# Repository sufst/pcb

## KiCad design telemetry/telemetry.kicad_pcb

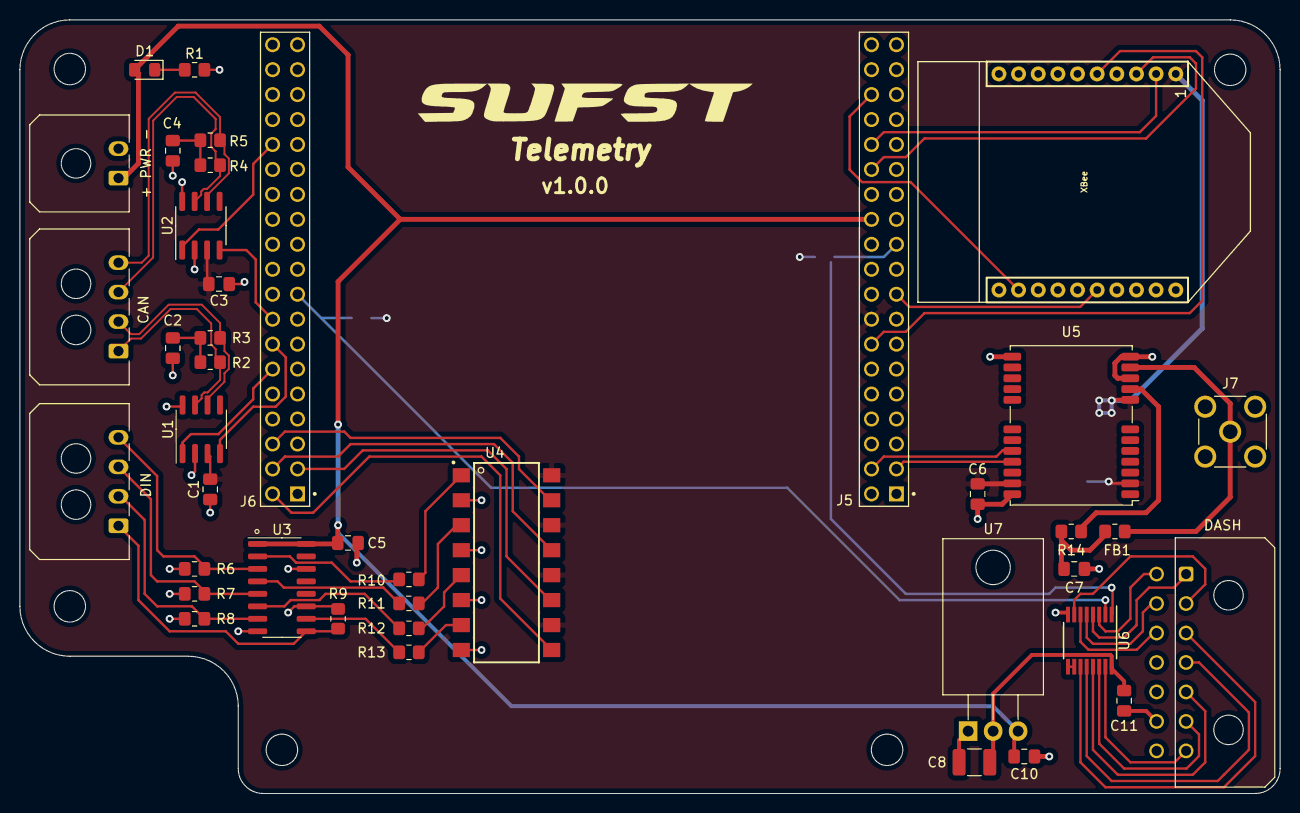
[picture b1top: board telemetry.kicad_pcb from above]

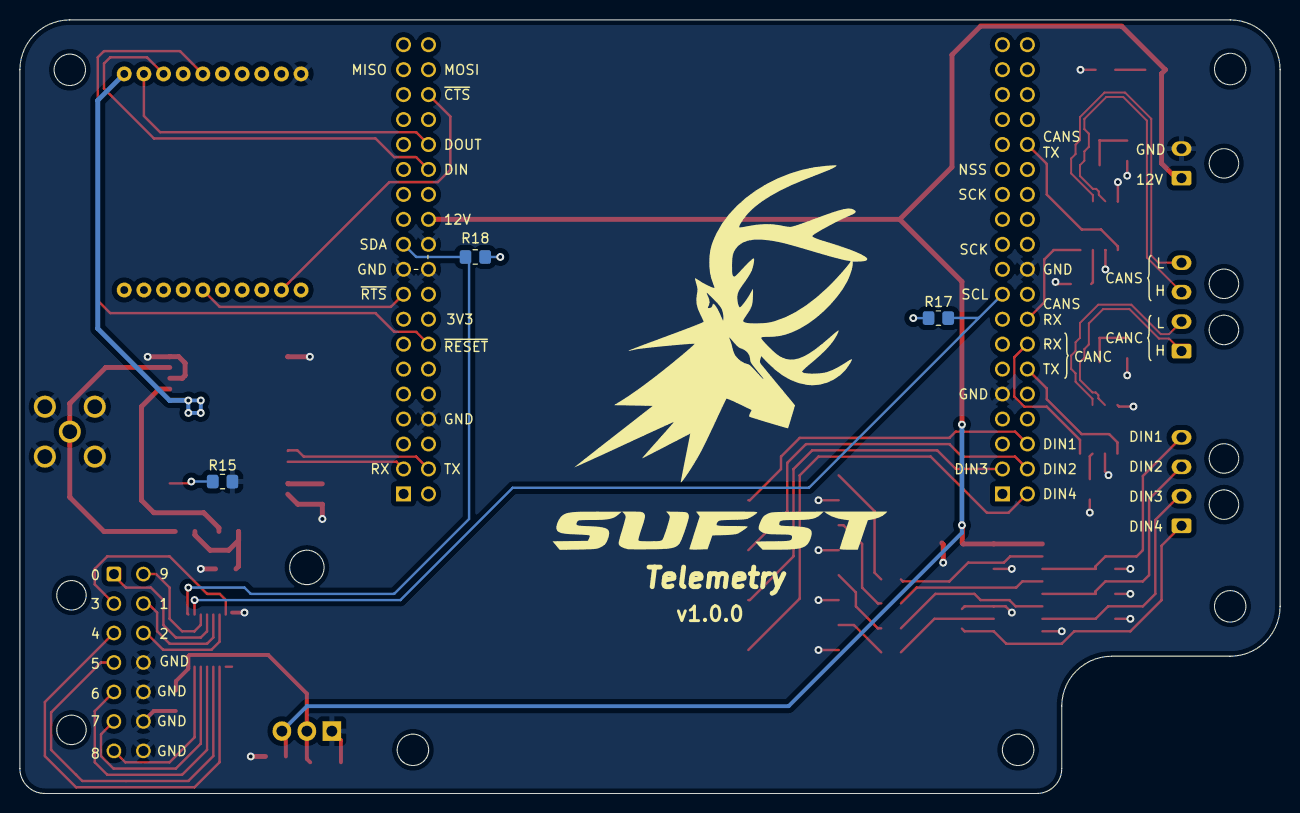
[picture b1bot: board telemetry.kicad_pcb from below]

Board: 2 copper layers, 128.3 x 78.7 mm, 49 parts (3 on the bottom side), 53 nets.

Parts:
C1, C3, C5, C10, C11: 100n; C_0805_2012Metric_Pad1.18x1.45mm_HandSolder
C2, C4: 4.7n; C_0805_2012Metric_Pad1.18x1.45mm_HandSolder
C6: 100nF; C_0805_2012Metric_Pad1.18x1.45mm_HandSolder
C7: 47pF; C_0805_2012Metric_Pad1.18x1.45mm_HandSolder
C8: 10u; C_1210_3225Metric_Pad1.33x2.70mm_HandSolder
D1: LED; LED_0805_2012Metric_Pad1.15x1.40mm_HandSolder
FB1: 120; R_0805_2012Metric_Pad1.20x1.40mm_HandSolder
H1, H2, H3, H4, H5: M3; MountingHole_3.2mm_M3
J1: PWR; Molex_Micro-Fit_3.0_43650-0200_1x02_P3.00mm_Horizontal
J2: MCU_DIN; Molex_Micro-Fit_3.0_43650-0400_1x04_P3.00mm_Horizontal
J3: CAN; Molex_Micro-Fit_3.0_43650-0400_1x04_P3.00mm_Horizontal
J4: XBee; XBEE
J5: CN7; NUCLEO-F446RE-2x19-CON
J6: CN10; NUCLEO-F446RE-2x19-CON
J7: Conn_Coaxial; SMA_Molex_73251-2200_Horizontal
J8: Dash 7 Segment; Molex_Micro-Fit_3.0_43045-1400_2x07_P3.00mm_Horizontal
R1: 3.3k; R_0805_2012Metric_Pad1.20x1.40mm_HandSolder
R2, R3, R4, R5: 60R; R_0805_2012Metric_Pad1.20x1.40mm_HandSolder
R6, R7, R8, R9: 10k; R_0805_2012Metric_Pad1.20x1.40mm_HandSolder
R10, R11, R12, R13: 1k; R_0805_2012Metric_Pad1.20x1.40mm_HandSolder
R14: 33; R_0805_2012Metric_Pad1.20x1.40mm_HandSolder
R15: DNP; R_0805_2012Metric_Pad1.20x1.40mm_HandSolder
R17, R18: 4k7; R_0805_2012Metric_Pad1.20x1.40mm_HandSolder
U1, U2: MAX3051ESA+; SOIC-8_3.9x4.9mm_P1.27mm
U3: HCF4010; SOIC-16_3.9x9.9mm_P1.27mm
U4: ILQ615-4X009T; SOIC254P1005X380-16N
U5: NEO-M9N; ublox_NEO
U6: MAX6958BAEE+T; QSOP-16_3.9x4.9mm_P0.635mm
U7: LD33CV; TO-220-3_Horizontal_TabDown

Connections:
+3V3: C1.2, C3.2, C6.2, J4.1, J5.16, R15.1, R17.1, R18.1, U1.3 (VDD), U2.3 (VDD), U4.10, U4.12, U4.14, U4.16, U5.2 (D_SEL), U5.8 (~RESET), U5.23 (VCC)
+12V: C5.2, C10.2, D1.2 (A), J1.1, J5.24, U3.1 (VCC), U3.16 (VDD), U7.3 (VI)
/3V3_LED: C8.1, C11.2, U6.16 (V+), U7.2 (VO)
/CAN-C Bus Transceiver/CAN_RX: J6.14, U1.4 (RXD)
/CAN-C Bus Transceiver/CAN_TX: J6.12, U1.1 (TXD)
/CAN-S Bus Transceiver/CAN_RX: J6.16, U2.4 (RXD)
/CAN-S Bus Transceiver/CAN_TX: J6.30, U2.1 (TXD)
/CAN_C+: J3.1, R2.2, U1.7 (CANH)
/CAN_C-: J3.2, R3.1, U1.6 (CANL)
/CAN_S+: J3.3, R4.2, U2.7 (CANH)
/CAN_S-: J3.4, R5.1, U2.6 (CANL)
/GPS/GPS_RX: J5.3, U5.21 (RXD/SPI_MOSI)
/GPS/GPS_TX: J5.4, U5.20 (TXD/SPI_MISO)
/SEG0: J8.1, U6.4 (DIG0/SEG0)
/SEG1: J8.9, U6.5 (DIG1/SEG1)
/SEG2: J8.10, U6.6 (DIG2/SEG2)
/SEG3: J8.2, U6.7 (DIG3/SEG3)
/SEG4: J8.3, U6.11 (SEG4)
/SEG5: J8.4, U6.12 (SEG5)
/SEG6: J8.5, U6.13 (SEG6)
/SEG7: J8.6, U6.14 (SEG7)
/SEG8: J8.7, U6.15 (SEG8)
/SEG9: J8.8, U6.3 (SEG9)
/XBee Module/DIN/`CONFIG/DIO14: J4.3, J5.28
/XBee Module/DOUT/DIO13: J4.2, J5.30
/XBee Module/~CTS: J4.12, J5.34
/XBee Module/~RESET: J4.5, J5.14
/XBee Module/~RTS: J4.16, J5.17
/input shift/DIN_1: J2.4, R6.2, U3.3 (Ain)
/input shift/DIN_2: J2.3, R7.2, U3.5 (Bin)
/input shift/DIN_3: J2.2, R8.2, U3.7 (Cin)
/input shift/DIN_4: J2.1, R9.2, U3.9 (Din)
/input shift/DOUT_1: J6.6, U4.15
/input shift/DOUT_2: J6.4, U4.13
/input shift/DOUT_3: J6.3, U4.11
/input shift/DOUT_4: J6.2, U4.9
/mcu/I2C1_SCL: J6.17, R17.2, U6.2 (SCL)
/mcu/I2C1_SDA: J5.21, R18.2, U6.1 (SDA)
GND: C1.1, C2.2, C3.1, C4.2, C5.1, C6.1, C7.1, C8.2, C10.1, C11.1, J1.2, J4.10, J5.8, J5.19, J5.20, J5.22, J6.9, J6.20, J7.2 (Ext), J8.11, J8.12, J8.13, J8.14, R1.2, R6.1, R7.1, R8.1, R9.1, R15.2, U1.2 (GND), U1.8 (RS), U2.2 (GND), U2.8 (RS), U3.8 (VSS), U3.11 (Ein), U3.14 (Fin), U4.2, U4.4, U4.6, U4.8, U5.10 (GND), U5.12 (GND), U5.13 (GND), U5.24 (GND), U6.8 (GND), U7.1 (GND)
unnamed: C2.1, R2.1, R3.2
unnamed: C4.1, R4.1, R5.2
unnamed: C7.2, FB1.1, R14.2
unnamed: D1.1 (K), R1.1
unnamed: FB1.2, J7.1 (In), U5.11 (RF_IN)
unnamed: R10.1, U3.2 (Aout)
unnamed: R10.2, U4.1
unnamed: R11.1, U3.4 (Bout)
unnamed: R11.2, U4.3
unnamed: R12.1, U3.6 (Cout)
unnamed: R12.2, U4.5
unnamed: R13.1, U3.10 (Dout)
unnamed: R13.2, U4.7
unnamed: R14.1, U5.9 (VCC_RF)

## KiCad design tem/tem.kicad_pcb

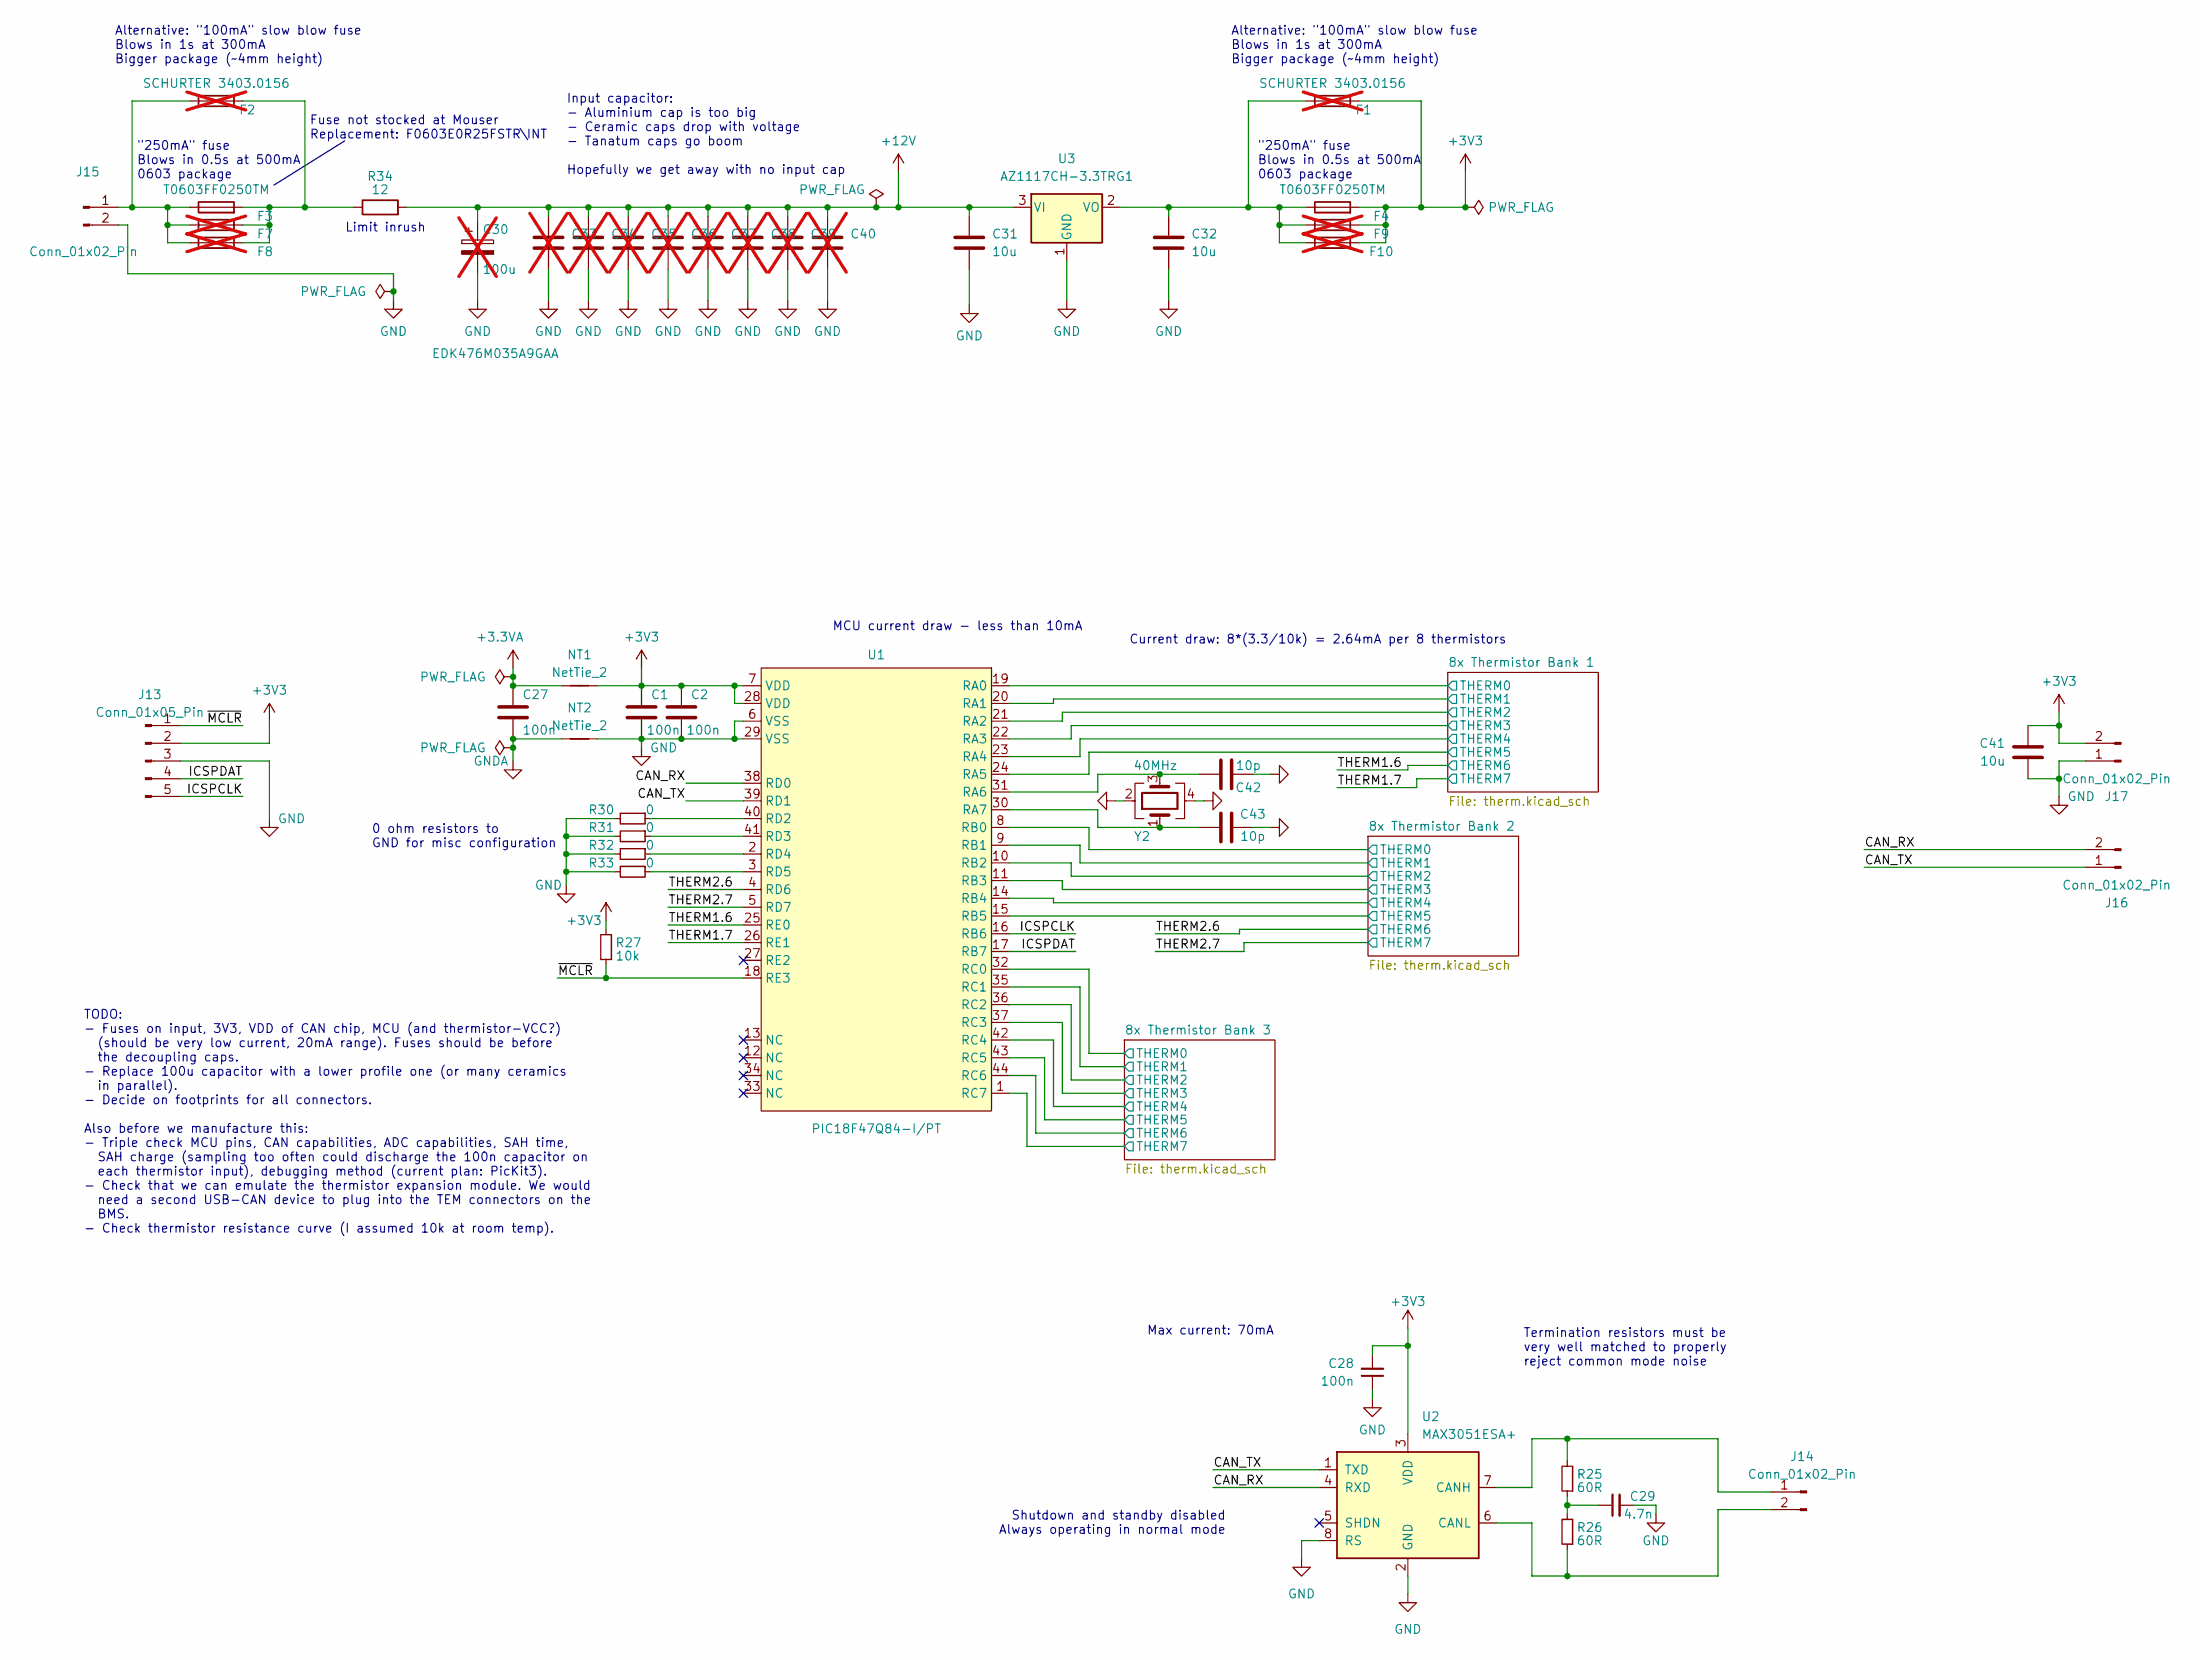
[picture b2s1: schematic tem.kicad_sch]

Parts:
C1, C2, C27, C28: 100n; C_0805_2012Metric_Pad1.18x1.45mm_HandSolder
C29: 4.7n; C_0805_2012Metric_Pad1.18x1.45mm_HandSolder
C30: 100u; CP_Elec_6.3x5.4; Part EDK476M035A9GAA; not fitted
C31, C32, C41: 10u; C_0805_2012Metric_Pad1.18x1.45mm_HandSolder
C33, C34, C35, C36, C37, C38, C39, C40: C_1206_3216Metric_Pad1.33x1.80mm_HandSolder; not fitted
C42, C43: 10p; C_0603_1608Metric_Pad1.08x0.95mm_HandSolder
F1, F2: SCHURTER 3403.0156; Fuse_Schurter_UMT250; not fitted
F3, F4: T0603FF0250TM; Fuse_0603_1608Metric_Pad1.05x0.95mm_HandSolder
F7, F8, F9, F10: T0603FF0250TM; Fuse_0603_1608Metric_Pad1.05x0.95mm_HandSolder; not fitted
J13: Conn_01x05_Pin; Conn5_SMD
J14, J15, J16, J17: Conn_01x02_Pin; Conn2_SMD
NT1, NT2: NetTie_2; R_0805_2012Metric_Pad1.20x1.40mm_HandSolder
R25, R26: 60R; R_0805_2012Metric_Pad1.20x1.40mm_HandSolder
R27: 10k; R_0805_2012Metric_Pad1.20x1.40mm_HandSolder
R30, R31, R32, R33: 0; R_0805_2012Metric_Pad1.20x1.40mm_HandSolder
R34: 12; R_0805_2012Metric_Pad1.20x1.40mm_HandSolder
U1: PIC18F47Q84-I/PT; TQFP-44_10x10mm_P0.8mm
U2: MAX3051ESA+; SOIC-8_3.9x4.9mm_P1.27mm
U3: AZ1117CH-3.3TRG1; SOT-223-3_TabPin2
Y2: 40MHz; Crystal_SMD_SeikoEpson_FA128-4Pin_2.0x1.6mm

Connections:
+3.3VA: C27.1, NT1.1; also elsewhere on the board
+3V3: C1.1, C2.1, C28.2, C41.1, F1.2, F4.2, F9.2, F10.2, J13.2, J17.2, NT1.2, R27.2, U1.7 (VDD), U1.28 (VDD), U2.3 (VDD)
+12V: C30.1, C31.1, C33.1, C34.1, C35.1, C36.1, C37.1, C38.1, C39.1, C40.1, R34.2, U3.3 (VI)
/8x Thermistor Bank 1/THERM0: U1.19 (RA0); also elsewhere on the board
/8x Thermistor Bank 1/THERM1: U1.20 (RA1); also elsewhere on the board
/8x Thermistor Bank 1/THERM2: U1.21 (RA2); also elsewhere on the board
/8x Thermistor Bank 1/THERM3: U1.22 (RA3); also elsewhere on the board
/8x Thermistor Bank 1/THERM4: U1.23 (RA4); also elsewhere on the board
/8x Thermistor Bank 1/THERM5: U1.24 (RA5); also elsewhere on the board
/8x Thermistor Bank 1/THERM6: C42.1, U1.31 (RA6), Y2.3; also elsewhere on the board
/8x Thermistor Bank 1/THERM7: C43.1, U1.30 (RA7), Y2.1; also elsewhere on the board
/8x Thermistor Bank 2/THERM0: U1.8 (RB0); also elsewhere on the board
/8x Thermistor Bank 2/THERM1: U1.9 (RB1); also elsewhere on the board
/8x Thermistor Bank 2/THERM2: U1.10 (RB2); also elsewhere on the board
/8x Thermistor Bank 2/THERM3: U1.11 (RB3); also elsewhere on the board
/8x Thermistor Bank 2/THERM4: U1.14 (RB4); also elsewhere on the board
/8x Thermistor Bank 2/THERM5: U1.15 (RB5); also elsewhere on the board
/8x Thermistor Bank 3/THERM0: U1.32 (RC0); also elsewhere on the board
/8x Thermistor Bank 3/THERM1: U1.35 (RC1); also elsewhere on the board
/8x Thermistor Bank 3/THERM2: U1.36 (RC2); also elsewhere on the board
/8x Thermistor Bank 3/THERM3: U1.37 (RC3); also elsewhere on the board
/8x Thermistor Bank 3/THERM4: U1.42 (RC4); also elsewhere on the board
/8x Thermistor Bank 3/THERM5: U1.43 (RC5); also elsewhere on the board
/8x Thermistor Bank 3/THERM6: U1.44 (RC6); also elsewhere on the board
/8x Thermistor Bank 3/THERM7: U1.1 (RC7); also elsewhere on the board
/CAN_RX: J16.2, U1.38 (RD0), U2.4 (RXD)
/CAN_TX: J16.1, U1.39 (RD1), U2.1 (TXD)
/ICSPCLK: J13.5, U1.16 (RB6)
/ICSPDAT: J13.4, U1.17 (RB7)
/THERM2.6: U1.4 (RD6); also elsewhere on the board
/THERM2.7: U1.5 (RD7); also elsewhere on the board
/~MCLR: J13.1, R27.1, U1.18 (RE3)
GND: C1.2, C2.2, C28.1, C29.2, C30.2, C31.2, C32.2, C33.2, C34.2, C35.2, C36.2, C37.2, C38.2, C39.2, C40.2, C41.2, J13.3, J15.2, J17.1, NT2.2, R30.2, R31.2, R32.2, R33.2, U1.6 (VSS), U1.29 (VSS), U2.2 (GND), U2.8 (RS), U3.1 (GND)
GNDA: C27.2, NT2.1; also elsewhere on the board
unnamed: C29.1, R25.1, R26.2
unnamed: F2.2, F3.2, F7.2, F8.2, R34.1
unnamed: J14.1, R25.2, U2.7 (CANH)
unnamed: J14.2, R26.1, U2.6 (CANL)
unnamed: F2.1, F3.1, F7.1, F8.1, J15.1
unnamed: R30.1, U1.40 (RD2)
unnamed: R31.1, U1.41 (RD3)
unnamed: R32.1, U1.2 (RD4)
unnamed: R33.1, U1.3 (RD5)
unnamed: C32.1, F1.1, F4.1, F9.1, F10.1, U3.2 (VO)

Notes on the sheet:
Alternative: "100mA" slow blow fuse Blows in 1s at 300mA Bigger package (~4mm height)
MCU current draw - less than 10mA
Max current: 70mA
Shutdown and standby disabled Always operating in normal mode
"250mA" fuse Blows in 0.5s at 500mA 0603 package
Input capacitor: - Aluminium cap is too big - Ceramic caps drop with voltage - Tanatum caps go boom Hopefully we get away with no input cap
Current draw: 8*(3.3/10k) = 2.64mA per 8 thermistors
0 ohm resistors to GND for misc configuration
TODO: - Fuses on input, 3V3, VDD of CAN chip, MCU (and thermistor-VCC?) (should be very low current, 20mA range). Fuses should be before the decoupling caps. - Replace 100u capacitor with a lower profile one (or many ceramics in parallel). - Decide on footprints for all connectors. Also before we m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
Fuse not stocked at Mouser Replacement: F0603E0R25FSTR\INT
Limit inrush
Termination resistors must be very well matched to properly reject common mode noise

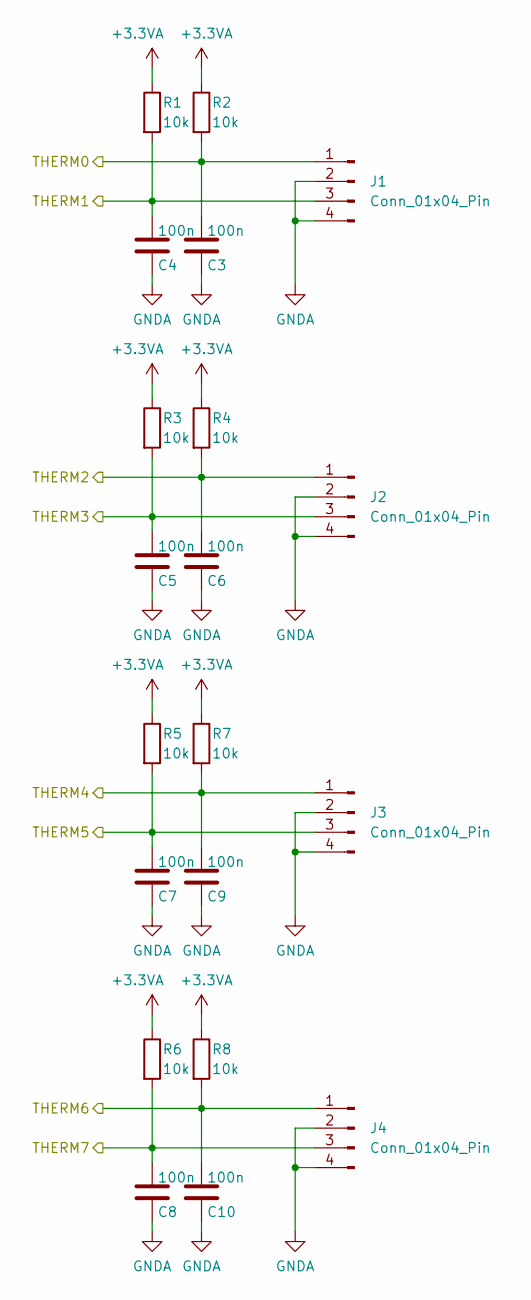
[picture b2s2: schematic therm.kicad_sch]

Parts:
C3, C4, C5, C6, C7, C8, C9, C10: 100n; C_0805_2012Metric_Pad1.18x1.45mm_HandSolder
J1, J2, J3, J4: Conn_01x04_Pin; Thermistor_x2
R1, R2, R3, R4, R5, R6, R7, R8: 10k; R_0805_2012Metric_Pad1.20x1.40mm_HandSolder

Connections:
+3.3VA: R1.1, R2.1, R3.1, R4.1, R5.1, R6.1, R7.1, R8.1; also elsewhere on the board
/8x Thermistor Bank 1/THERM0: C3.1, J1.1, R2.2; also elsewhere on the board
/8x Thermistor Bank 1/THERM1: C4.1, J1.3, R1.2; also elsewhere on the board
/8x Thermistor Bank 1/THERM2: C6.1, J2.1, R4.2; also elsewhere on the board
/8x Thermistor Bank 1/THERM3: C5.1, J2.3, R3.2; also elsewhere on the board
/8x Thermistor Bank 1/THERM4: C9.1, J3.1, R7.2; also elsewhere on the board
/8x Thermistor Bank 1/THERM5: C7.1, J3.3, R5.2; also elsewhere on the board
/8x Thermistor Bank 1/THERM6: C10.1, J4.1, R8.2; also elsewhere on the board
/8x Thermistor Bank 1/THERM7: C8.1, J4.3, R6.2; also elsewhere on the board
GNDA: C3.2, C4.2, C5.2, C6.2, C7.2, C8.2, C9.2, C10.2, J1.2, J1.4, J2.2, J2.4, J3.2, J3.4, J4.2, J4.4; also elsewhere on the board

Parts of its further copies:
C11, C12, C13, C14, C15, C16, C17, C18, C19, C20, C21, C22, C23, C24, C25, C26: 100n; C_0805_2012Metric_Pad1.18x1.45mm_HandSolder
J5, J6, J7, J8, J9, J10, J11, J12: Conn_01x04_Pin; Thermistor_x2
R9, R10, R11, R12, R13, R14, R15, R16, R17, R18, R19, R20, R21, R22, R23, R24: 10k; R_0805_2012Metric_Pad1.20x1.40mm_HandSolder

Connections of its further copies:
+3.3VA: R9.1, R10.1, R11.1, R12.1, R13.1, R14.1, R15.1, R16.1, R17.1, R18.1, R19.1, R20.1, R21.1, R22.1, R23.1, R24.1; also elsewhere on the board
/8x Thermistor Bank 2/THERM0: C15.1, J5.1, R13.2; also elsewhere on the board
/8x Thermistor Bank 2/THERM1: C11.1, J5.3, R9.2; also elsewhere on the board
/8x Thermistor Bank 2/THERM2: C16.1, J6.1, R14.2; also elsewhere on the board
/8x Thermistor Bank 2/THERM3: C12.1, J6.3, R10.2; also elsewhere on the board
/8x Thermistor Bank 2/THERM4: C17.1, J7.1, R15.2; also elsewhere on the board
/8x Thermistor Bank 2/THERM5: C13.1, J7.3, R11.2; also elsewhere on the board
/8x Thermistor Bank 3/THERM0: C23.1, J9.1, R21.2; also elsewhere on the board
/8x Thermistor Bank 3/THERM1: C19.1, J9.3, R17.2; also elsewhere on the board
/8x Thermistor Bank 3/THERM2: C24.1, J10.1, R22.2; also elsewhere on the board
/8x Thermistor Bank 3/THERM3: C20.1, J10.3, R18.2; also elsewhere on the board
/8x Thermistor Bank 3/THERM4: C25.1, J11.1, R23.2; also elsewhere on the board
/8x Thermistor Bank 3/THERM5: C21.1, J11.3, R19.2; also elsewhere on the board
/8x Thermistor Bank 3/THERM6: C26.1, J12.1, R24.2; also elsewhere on the board
/8x Thermistor Bank 3/THERM7: C22.1, J12.3, R20.2; also elsewhere on the board
/THERM2.6: C18.1, J8.1, R16.2; also elsewhere on the board
/THERM2.7: C14.1, J8.3, R12.2; also elsewhere on the board
GNDA: C11.2, C12.2, C13.2, C14.2, C15.2, C16.2, C17.2, C18.2, C19.2, C20.2, C21.2, C22.2, C23.2, C24.2, C25.2, C26.2, J5.2, J5.4, J6.2, J6.4, J7.2, J7.4, J8.2, J8.4, J9.2, J9.4, J10.2, J10.4, J11.2, J11.4, J12.2, J12.4; also elsewhere on the board

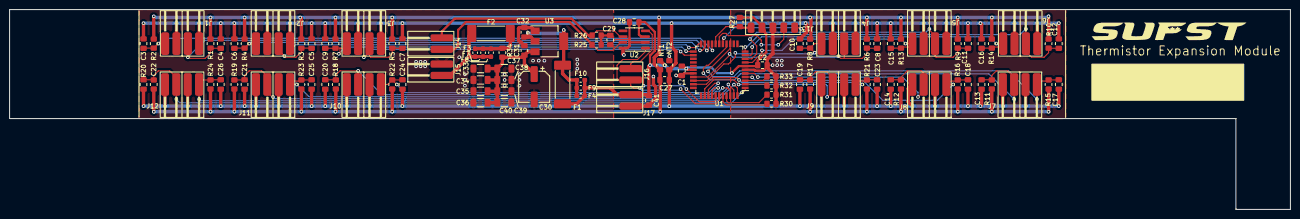
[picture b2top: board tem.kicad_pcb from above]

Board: 2 copper layers, 282.0 x 44.0 mm, 103 parts (0 on the bottom side), 44 nets.

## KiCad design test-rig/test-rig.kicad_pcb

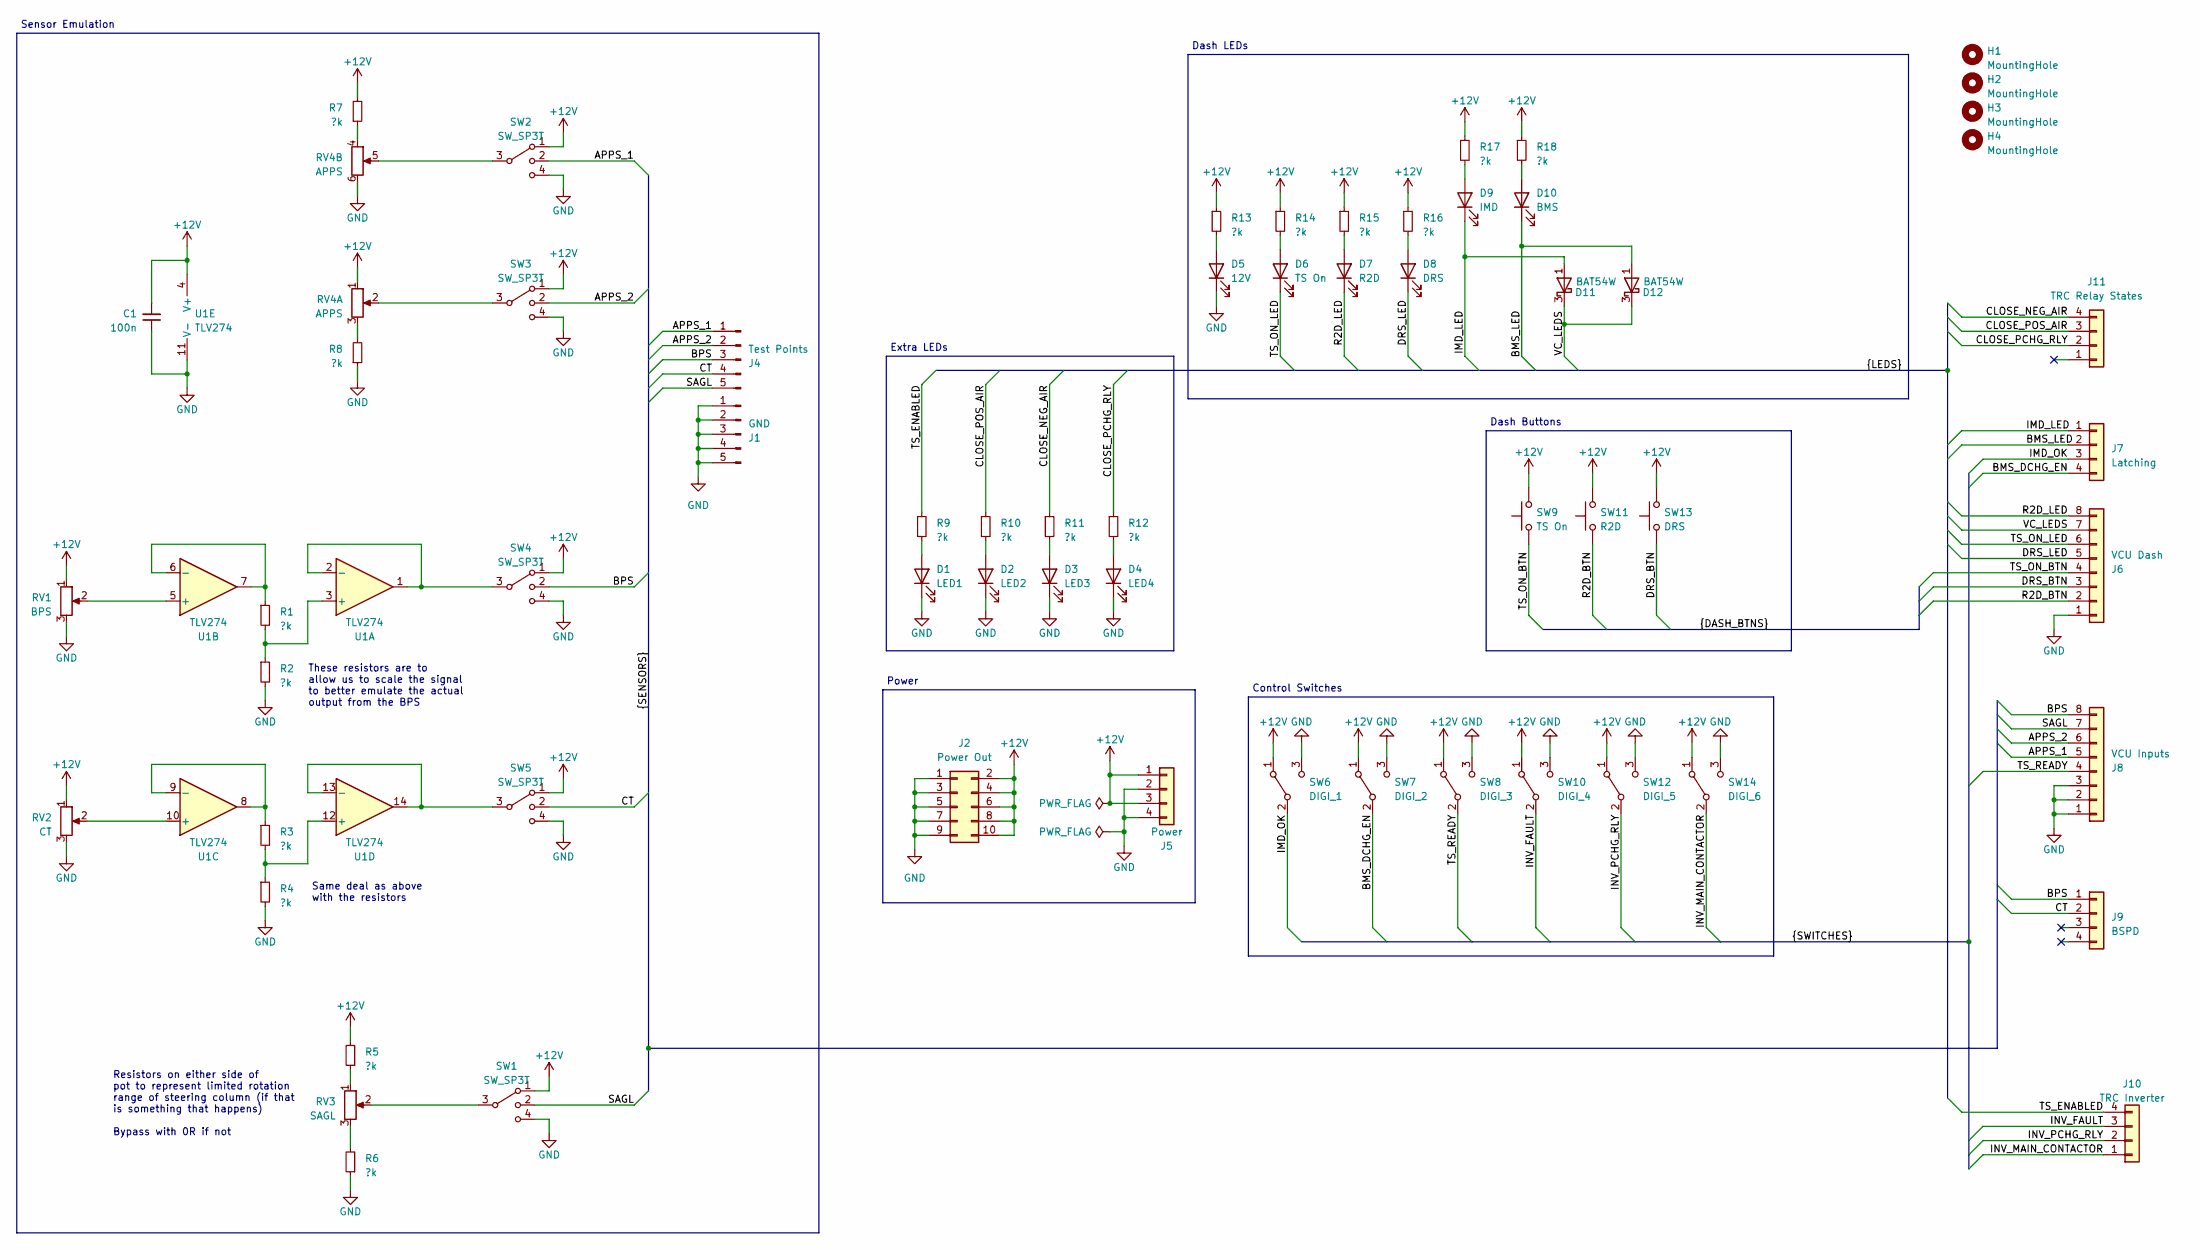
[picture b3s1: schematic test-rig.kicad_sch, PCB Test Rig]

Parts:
C1: 100n; C_0805_2012Metric_Pad1.18x1.45mm_HandSolder
D1: LED1; LED_0805_2012Metric_Pad1.15x1.40mm_HandSolder
D2: LED2; LED_0805_2012Metric_Pad1.15x1.40mm_HandSolder
D3: LED3; LED_0805_2012Metric_Pad1.15x1.40mm_HandSolder
D4: LED4; LED_0805_2012Metric_Pad1.15x1.40mm_HandSolder
D5: 12V; LED_D5.0mm
D6: TS On; LED_D5.0mm
D7: R2D; LED_D5.0mm
D8: DRS; LED_D5.0mm
D9: IMD; LED_D5.0mm
D10: BMS; LED_D5.0mm
D11, D12: BAT54W; SOT-323_SC-70
H1, H2, H3, H4: MountingHole; MountingHole_4.3mm_M4
J1: GND; PinHeader_1x05_P2.54mm_Vertical
J2: Power Out; PinHeader_2x05_P2.54mm_Vertical
J4: Test Points; PinHeader_1x05_P2.54mm_Vertical
J5: Power; Molex_Micro-Fit_3.0_43045-0400_2x02_P3.00mm_Horizontal
J6: VCU Dash; Molex_Micro-Fit_3.0_43045-0800_2x04_P3.00mm_Horizontal
J7: Latching; Molex_Micro-Fit_3.0_43045-0400_2x02_P3.00mm_Horizontal
J8: VCU Inputs; Molex_Micro-Fit_3.0_43045-0800_2x04_P3.00mm_Horizontal
J9: BSPD; Molex_Micro-Fit_3.0_43045-0400_2x02_P3.00mm_Horizontal
J10: TRC Inverter; Molex_Micro-Fit_3.0_43045-0400_2x02_P3.00mm_Horizontal
J11: TRC Relay States; Molex_Micro-Fit_3.0_43045-0400_2x02_P3.00mm_Horizontal
R1, R2, R3, R4, R5, R6, R7, R8, R9, R10, R11, R12, R13, R14, R15, R16, R17, R18: ?k; R_0805_2012Metric_Pad1.20x1.40mm_HandSolder
RV1: BPS; Potentiometer_Alps_RK09K_Single_Vertical
RV2: CT; Potentiometer_Alps_RK09K_Single_Vertical
RV3: SAGL; Potentiometer_Alps_RK09K_Single_Vertical
RV4: APPS; Potentiometer_Alpha_RD902F-40-00D_Dual_Vertical
SW1, SW2, SW3, SW4, SW5: SW_SP3T; SS14MDP2_NKK
SW6: DIGI_1; SW_OS102011MS2QN1
SW7: DIGI_2; SW_OS102011MS2QN1
SW8: DIGI_3; SW_OS102011MS2QN1
SW9: TS On; KSA_Tactile_SPST
SW10: DIGI_4; SW_OS102011MS2QN1
SW11: R2D; KSA_Tactile_SPST
SW12: DIGI_5; SW_OS102011MS2QN1
SW13: DRS; KSA_Tactile_SPST
SW14: DIGI_6; SW_OS102011MS2QN1
U1: TLV274; SOIC-14_3.9x8.7mm_P1.27mm

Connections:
+12V: C1.2, J2.2, J2.4, J2.6, J2.8, J2.10, J5.1, J5.3, R5.2, R7.2, R13.1, R14.1, R15.1, R16.1, R17.1, R18.1, RV1.1, RV2.1, RV4.1, SW1.1, SW2.1, SW3.1, SW4.1, SW5.1, SW6.1 (A), SW7.1 (A), SW8.1 (A), SW9.2, SW10.1 (A), SW11.2, SW12.1 (A), SW13.2, SW14.1 (A), U1.4 (V+)
/APPS_1: J4.1, J8.5, SW2.2
/APPS_2: J4.2, J8.6, SW3.2
/BMS_DCHG_EN: J7.4, SW7.2 (B)
/BMS_LED: D10.1 (K), D12.1 (A), J7.2
/BPS: J4.3, J8.8, J9.1, SW4.2
/CLOSE_NEG_AIR: J11.4, R11.1
/CLOSE_PCHG_RLY: J11.2, R12.1
/CLOSE_POS_AIR: J11.3, R10.1
/CT: J4.4, J9.2, SW5.2
/DRS_BTN: J6.3, SW13.1
/DRS_LED: D8.1 (K), J6.5
/IMD_LED: D9.1 (K), D11.1 (A), J7.1
/IMD_OK: J7.3, SW6.2 (B)
/INV_FAULT: J10.3, SW10.2 (B)
/INV_MAIN_CONTACTOR: J10.1, SW14.2 (B)
/INV_PCHG_RLY: J10.2, SW12.2 (B)
/R2D_BTN: J6.2, SW11.1
/R2D_LED: D7.1 (K), J6.8
/SAGL: J4.5, J8.7, SW1.2
/TS_ENABLED: J10.4, R9.1
/TS_ON_BTN: J6.4, SW9.1
/TS_ON_LED: D6.1 (K), J6.6
/TS_READY: J8.4, SW8.2 (B)
/VC_LEDS: D11.3 (K), D12.3 (K), J6.7
GND: C1.1, D1.1 (K), D2.1 (K), D3.1 (K), D4.1 (K), D5.1 (K), J1.1, J1.2, J1.3, J1.4, J1.5, J2.1, J2.3, J2.5, J2.7, J2.9, J5.2, J5.4, J6.1, J8.1, J8.2, J8.3, R2.2, R4.2, R6.1, R8.1, RV1.3, RV2.3, RV4.6, SW1.4, SW2.4, SW3.4, SW4.4, SW5.4, SW6.3 (C), SW7.3 (C), SW8.3 (C), SW10.3 (C), SW12.3 (C), SW14.3 (C), U1.11 (V-)
unnamed: D1.2 (A), R9.2
unnamed: D2.2 (A), R10.2
unnamed: D3.2 (A), R11.2
unnamed: D4.2 (A), R12.2
unnamed: D5.2 (A), R13.2
unnamed: D6.2 (A), R14.2
unnamed: D7.2 (A), R15.2
unnamed: D8.2 (A), R16.2
unnamed: D9.2 (A), R17.2
unnamed: D10.2 (A), R18.2
unnamed: R5.1, RV3.1
unnamed: R6.2, RV3.3
unnamed: R7.1, RV4.4
unnamed: R8.2, RV4.3
unnamed: RV3.2, SW1.3
unnamed: RV4.2, SW3.3
unnamed: RV4.5, SW2.3
unnamed: R1.2, R2.1, U1.3 (+)
unnamed: SW4.3, U1.1, U1.2 (-)
unnamed: RV1.2, U1.5 (+)
unnamed: R1.1, U1.6 (-), U1.7
unnamed: RV2.2, U1.10 (+)
unnamed: R3.1, U1.8, U1.9 (-)
unnamed: R3.2, R4.1, U1.12 (+)
unnamed: SW5.3, U1.13 (-), U1.14

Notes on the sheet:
Dash Buttons
Resistors on either side of pot to represent limited rotation range of steering column (if that is something that happens) Bypass with 0R if not
Extra LEDs
Power
These resistors are to allow us to scale the signal to better emulate the actual output from the BPS
Same deal as above with the resistors
Sensor Emulation
Control Switches
Dash LEDs

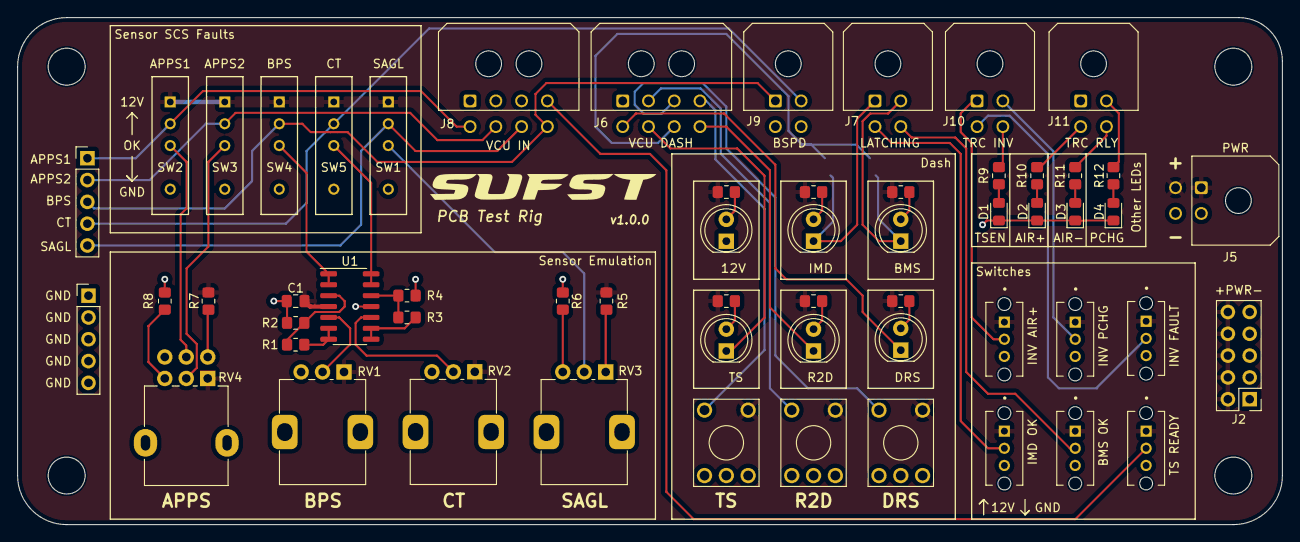
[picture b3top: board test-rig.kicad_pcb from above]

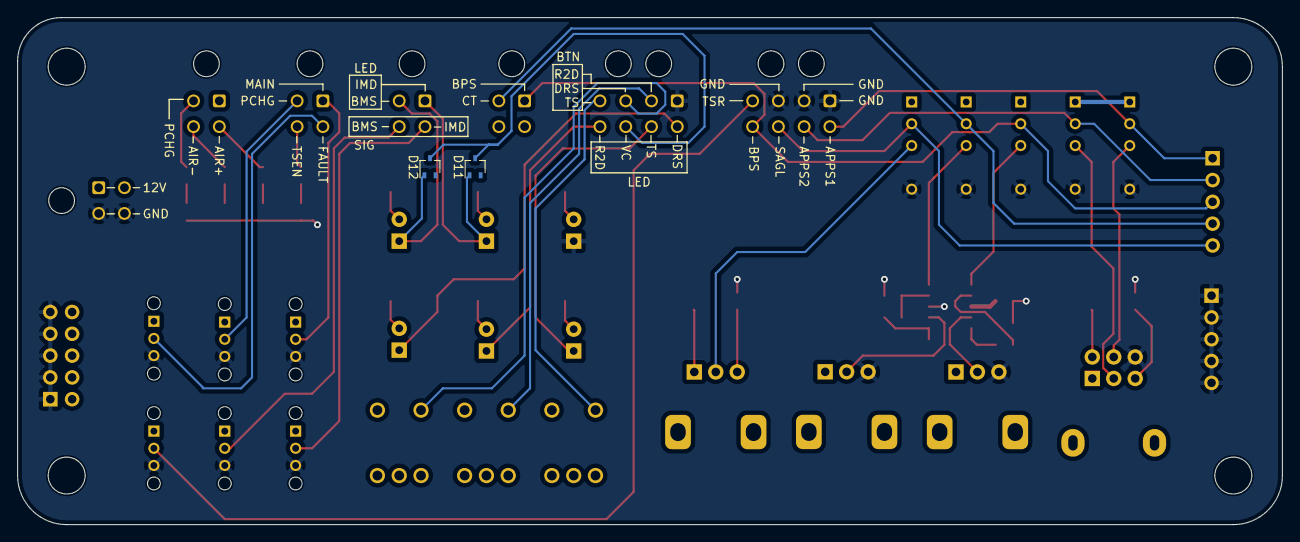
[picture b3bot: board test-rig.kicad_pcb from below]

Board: 2 copper layers, 147.3 x 59.1 mm, 64 parts (2 on the bottom side), 51 nets.
